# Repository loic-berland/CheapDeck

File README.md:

# CheapDeck
A QMK based macropad

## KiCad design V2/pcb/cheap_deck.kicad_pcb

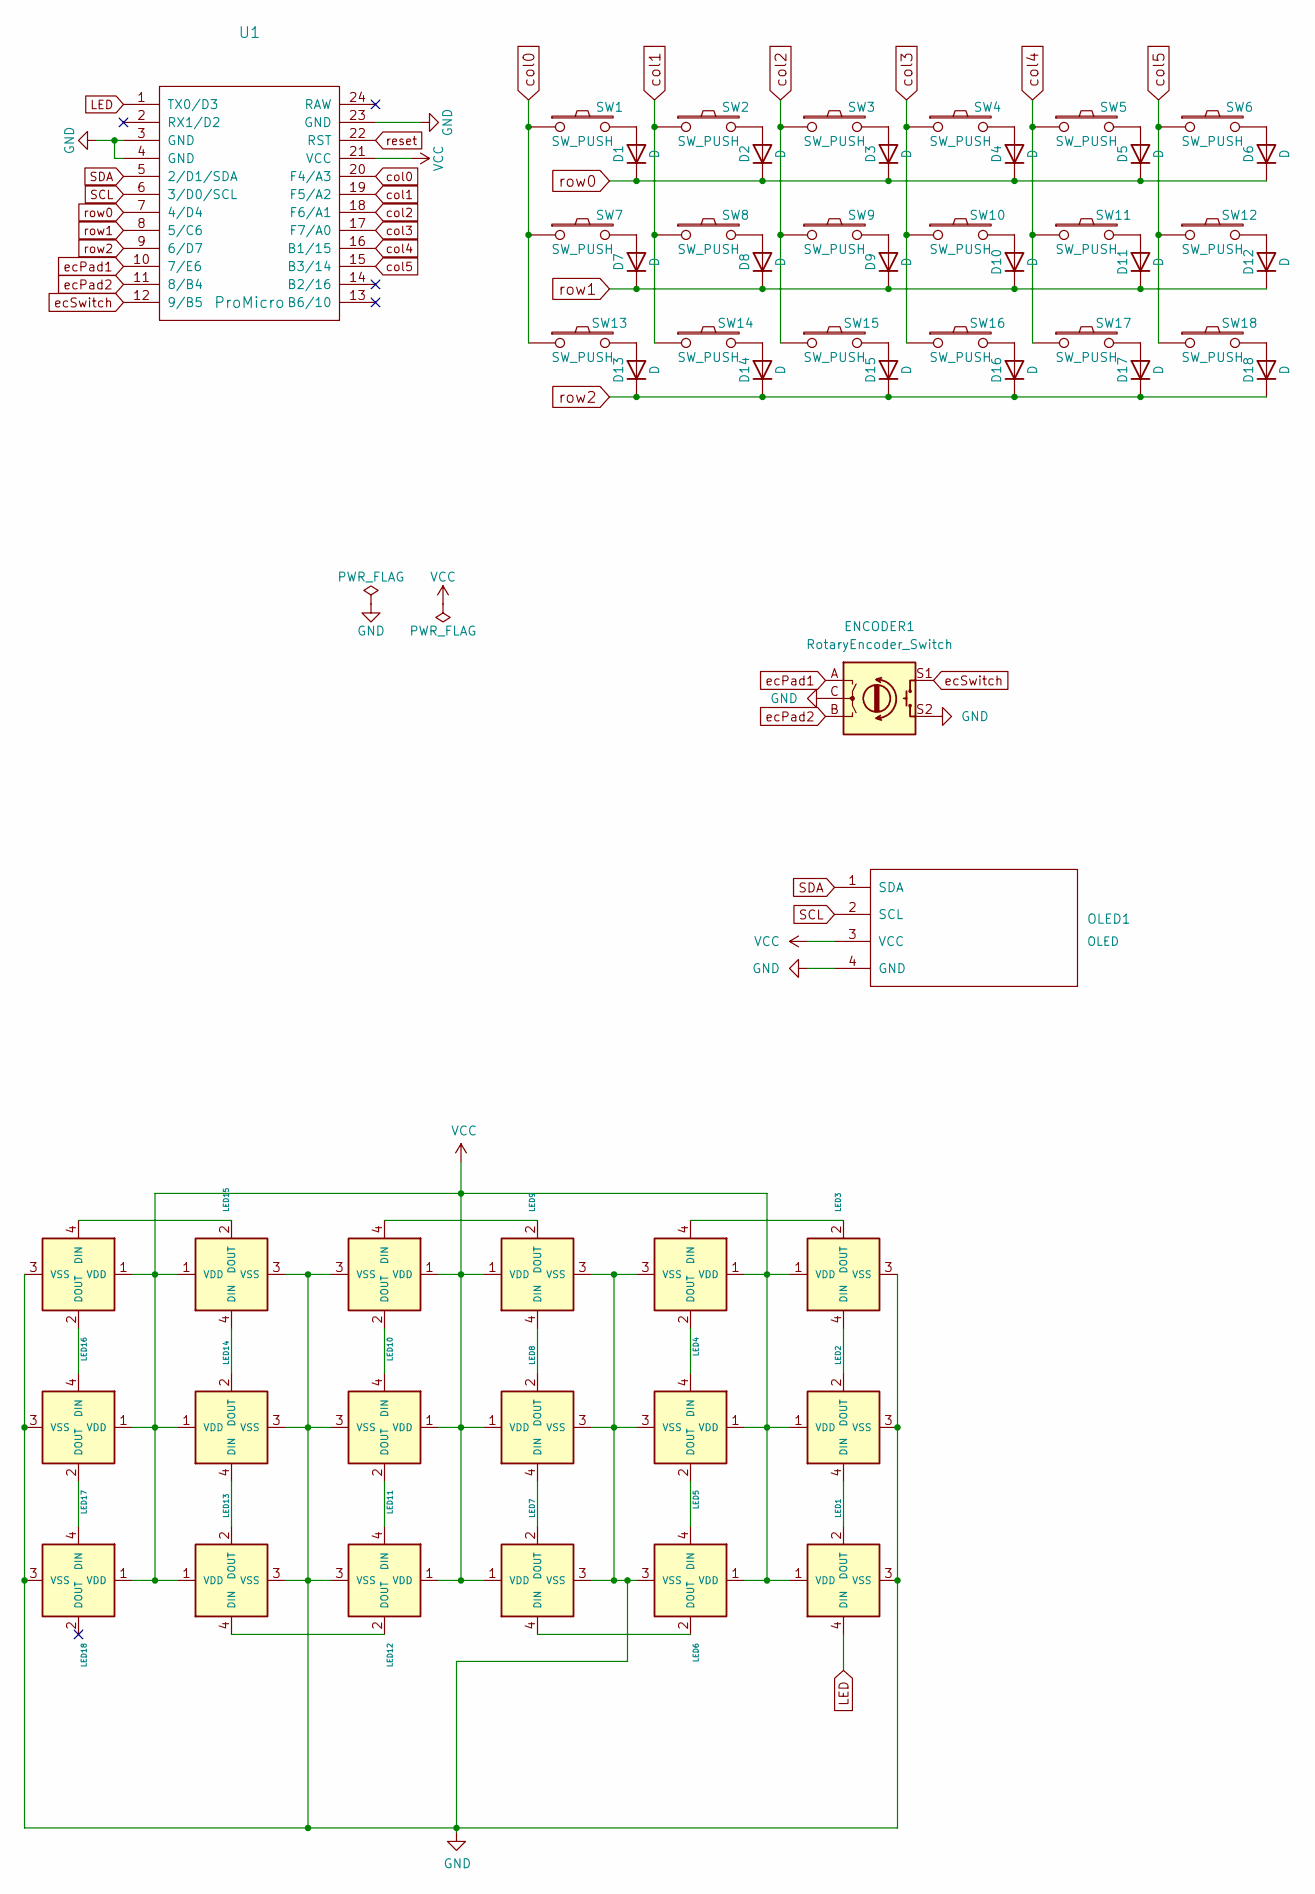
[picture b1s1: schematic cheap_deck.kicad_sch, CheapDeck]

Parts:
D1, D2, D3, D4, D5, D6, D7, D8, D9, D10, D11, D12, D13, D14, D15, D16, D17, D18: D; D3_SMD_v2
ENCODER1: RotaryEncoder_Switch; RotaryEncoder_Alps_EC11E-Switch_Vertical_H20mm_CircularMoun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
LED1, LED2, LED3, LED4, LED5, LED6, LED7, LED8, LED9, LED10, LED11, LED12, LED13, LED14, LED15, LED16, LED17, LED18: YS-SK6812MINI-E
OLED1: OLED; OLED_v2
SW1, SW2, SW3, SW4, SW5, SW6, SW7, SW8, SW9, SW10, SW11, SW12, SW13, SW14, SW15, SW16, SW17, SW18: SW_PUSH; CherryMX_Hotswap
U1: ProMicro; ProMicro_v3

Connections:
GND: ENCODER1.C, ENCODER1.S2, LED1.3 (VSS), LED2.3 (VSS), LED3.3 (VSS), LED4.3 (VSS), LED5.3 (VSS), LED6.3 (VSS), LED7.3 (VSS), LED8.3 (VSS), LED9.3 (VSS), LED10.3 (VSS), LED11.3 (VSS), LED12.3 (VSS), LED13.3 (VSS), LED14.3 (VSS), LED15.3 (VSS), LED16.3 (VSS), LED17.3 (VSS), LED18.3 (VSS), OLED1.4 (GND), U1.3 (GND), U1.4 (GND), U1.23 (GND)
LED: LED1.4 (DIN), U1.1 (TX0/D3)
unnamed: D1.2 (A), SW1.2
unnamed: D2.2 (A), SW2.2
unnamed: D3.2 (A), SW3.2
unnamed: D4.2 (A), SW4.2
unnamed: D5.2 (A), SW5.2
unnamed: D6.2 (A), SW6.2
unnamed: D7.2 (A), SW7.2
unnamed: D8.2 (A), SW8.2
unnamed: D9.2 (A), SW9.2
unnamed: D10.2 (A), SW10.2
unnamed: D11.2 (A), SW11.2
unnamed: D12.2 (A), SW12.2
unnamed: D13.2 (A), SW13.2
unnamed: D14.2 (A), SW14.2
unnamed: D15.2 (A), SW15.2
unnamed: D16.2 (A), SW16.2
unnamed: D17.2 (A), SW17.2
unnamed: D18.2 (A), SW18.2
unnamed: LED1.2 (DOUT), LED2.4 (DIN)
unnamed: LED2.2 (DOUT), LED3.4 (DIN)
unnamed: LED3.2 (DOUT), LED4.4 (DIN)
unnamed: LED4.2 (DOUT), LED5.4 (DIN)
unnamed: LED5.2 (DOUT), LED6.4 (DIN)
unnamed: LED6.2 (DOUT), LED7.4 (DIN)
unnamed: LED7.2 (DOUT), LED8.4 (DIN)
unnamed: LED8.2 (DOUT), LED9.4 (DIN)
unnamed: LED10.2 (DOUT), LED11.4 (DIN)
unnamed: LED9.2 (DOUT), LED10.4 (DIN)
unnamed: LED11.2 (DOUT), LED12.4 (DIN)
unnamed: LED12.2 (DOUT), LED13.4 (DIN)
unnamed: LED13.2 (DOUT), LED14.4 (DIN)
unnamed: LED14.2 (DOUT), LED15.4 (DIN)
unnamed: LED15.2 (DOUT), LED16.4 (DIN)
unnamed: LED16.2 (DOUT), LED17.4 (DIN)
unnamed: LED17.2 (DOUT), LED18.4 (DIN)
SCL: OLED1.2 (SCL), U1.6 (3/D0/SCL)
SDA: OLED1.1 (SDA), U1.5 (2/D1/SDA)
VCC: LED1.1 (VDD), LED2.1 (VDD), LED3.1 (VDD), LED4.1 (VDD), LED5.1 (VDD), LED6.1 (VDD), LED7.1 (VDD), LED8.1 (VDD), LED9.1 (VDD), LED10.1 (VDD), LED11.1 (VDD), LED12.1 (VDD), LED13.1 (VDD), LED14.1 (VDD), LED15.1 (VDD), LED16.1 (VDD), LED17.1 (VDD), LED18.1 (VDD), OLED1.3 (VCC), U1.21 (VCC)
col0: SW1.1, SW7.1, SW13.1, U1.20 (F4/A3)
col1: SW2.1, SW8.1, SW14.1, U1.19 (F5/A2)
col2: SW3.1, SW9.1, SW15.1, U1.18 (F6/A1)
col3: SW4.1, SW10.1, SW16.1, U1.17 (F7/A0)
col4: SW5.1, SW11.1, SW17.1, U1.16 (B1/15)
col5: SW6.1, SW12.1, SW18.1, U1.15 (B3/14)
ecPad1: ENCODER1.A, U1.10 (7/E6)
ecPad2: ENCODER1.B, U1.11 (8/B4)
ecSwitch: ENCODER1.S1, U1.12 (9/B5)
reset: U1.22 (RST)
row0: D1.1 (K), D2.1 (K), D3.1 (K), D4.1 (K), D5.1 (K), D6.1 (K), U1.7 (4/D4)
row1: D7.1 (K), D8.1 (K), D9.1 (K), D10.1 (K), D11.1 (K), D12.1 (K), U1.8 (5/C6)
row2: D13.1 (K), D14.1 (K), D15.1 (K), D16.1 (K), D17.1 (K), D18.1 (K), U1.9 (6/D7)

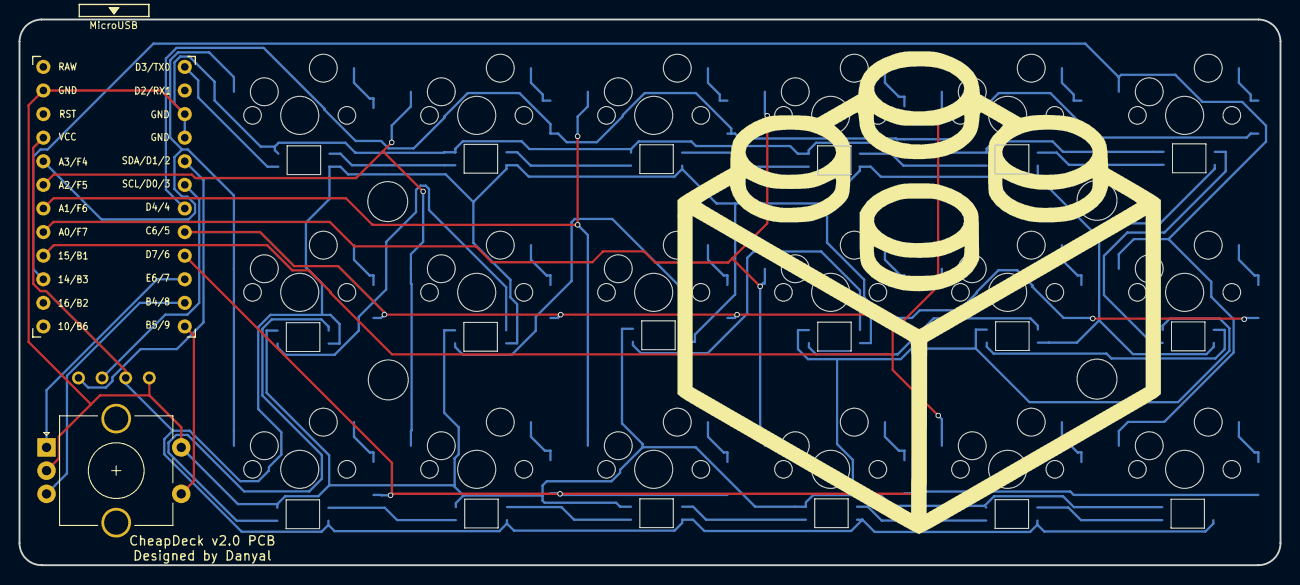
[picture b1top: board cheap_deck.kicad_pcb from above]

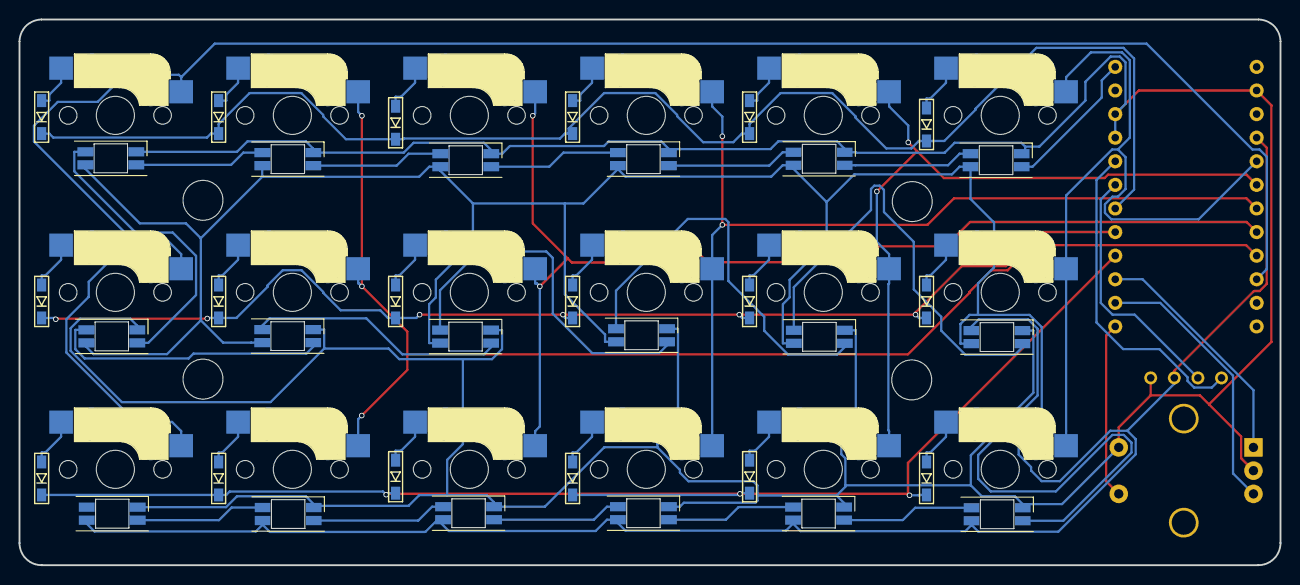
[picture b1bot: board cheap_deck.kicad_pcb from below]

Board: 2 copper layers, 135.7 x 58.7 mm, 61 parts (36 on the bottom side), 52 nets.

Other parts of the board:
mountingHole1, mountingHole2, mountingHole3, mountingHole4: MountingHole_4.3mm_M4

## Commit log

2022-02-27 Added V1 Case files
2022-02-27 Update .gitignore and README
2022-02-27 Added PCB files
2022-07-03 Added V2 and changed repo structure
